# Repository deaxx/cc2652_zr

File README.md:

# cc2652_zr
ZB router on module E72-2G4M20S1E

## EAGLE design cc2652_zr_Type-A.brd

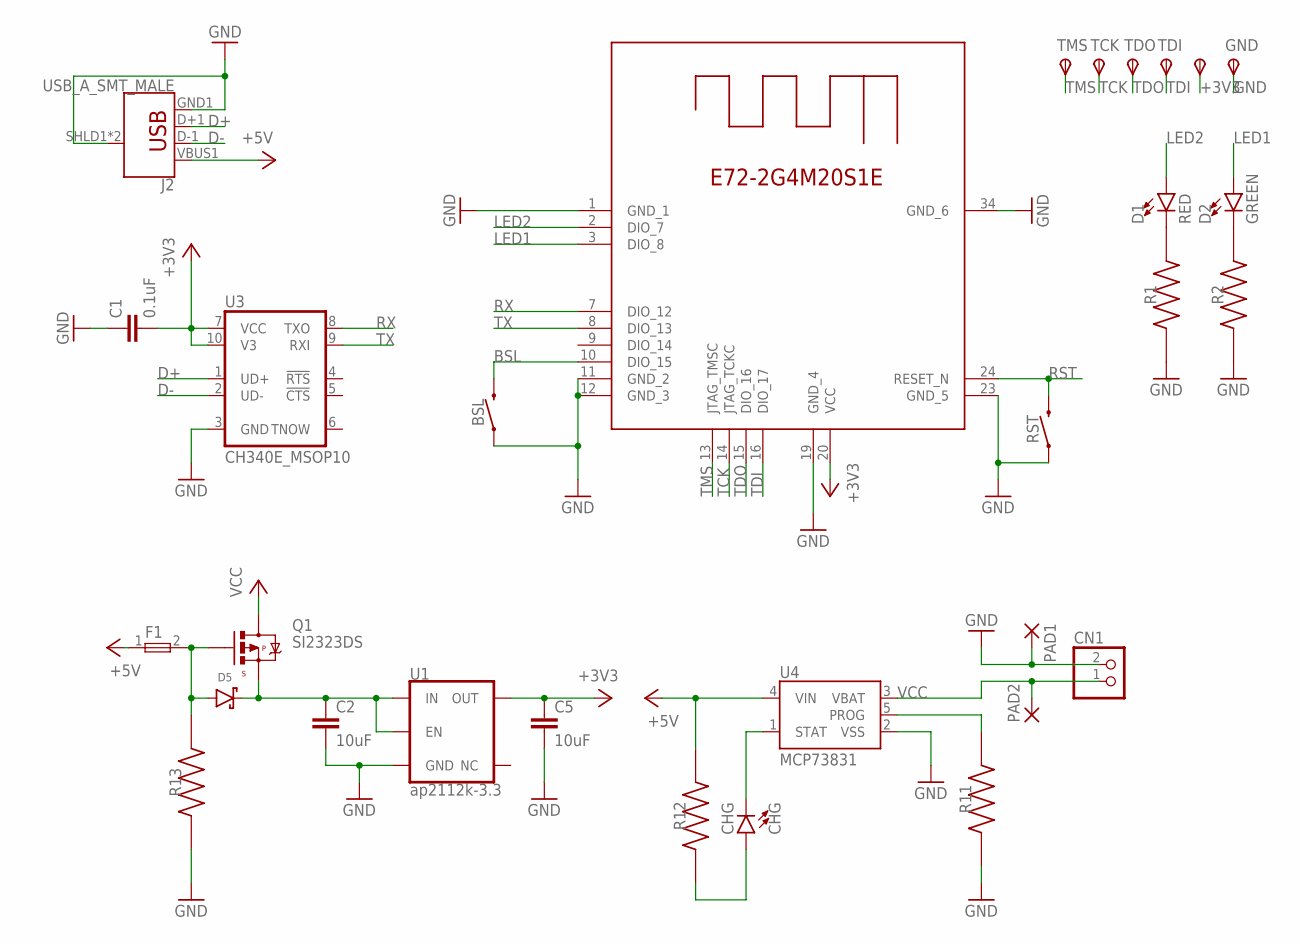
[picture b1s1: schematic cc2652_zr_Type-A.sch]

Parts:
+3V3: TPSTP11R; TP11R
BSL: MOMENTARY-SWITCH-SPST-SMD-4.6X2.8MM; TACTILE_SWITCH_SMD_4.6X2.8MM
C1: 0.1uF; 0603
C2, C5: 10uF; 0603
CHG: CHG; LED-0603
CN1: JST_2PIN-SMT-RA; JST-PH-2-SMT-RA
D1: RED; LED-0603
D2: GREEN; LED-0603
D5: DIODE-SCHOTTKY; SOD-323
F1: FEMTOSMDC016F-02; RESC1608X50N
GND: TPSTP11R; TP11R
J2: USB_A_SMT_MALE; USB-A-SMT-MALE
PAD1, PAD2: WIREPADSMD1,27-254; SMD1,27-2,54
Q1: SI2323DS; SOT23
R1, R2, R12: 2.2k; RESC1005X40N
R11: 2k; RESC1005X40N
R13: 10k; RESC1005X40N
RST: MOMENTARY-SWITCH-SPST-SMD-4.6X2.8MM; TACTILE_SWITCH_SMD_4.6X2.8MM
TCK: TPSTP11R; TP11R
TDI: TPSTP11R; TP11R
TDO: TPSTP11R; TP11R
TMS: TPSTP11R; TP11R
U1: ap2112k-3.3; SOT23-5
U3: CH340E_MSOP10; MSOP10
U4: MCP73831; SOT23-5
U$1: E72-2G4M20S1E

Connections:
+3V3: +3V3.TP, C1.2, C5.1, U1.5 (OUT), U3.7 (VCC), U3.10 (V3), U$1.20 (VCC)
+5V: F1.1, J2.VBUS1 (VBUS), R12.2, U4.4 (VIN)
BSL: BSL.3 (2), BSL.4 (2), U$1.10 (DIO_15)
D+: J2.D+1 (D+), U3.1 (UD+)
D-: J2.D-1 (D-), U3.2 (UD-)
GND: BSL.1, BSL.2 (1), C1.1, C2.2, C5.2, CN1.2 (1), GND.TP, J2.GND1 (GND), J2.SHLD1 (SHIELD), J2.SHLD2 (SHIELD), PAD1.1, R1.1, R2.1, R11.1, R13.1, RST.1, RST.2 (1), U1.2 (GND), U3.3 (GND), U4.2 (VSS), U$1.1 (GND_1), U$1.11 (GND_2), U$1.12 (GND_3), U$1.19 (GND_4), U$1.23 (GND_5), U$1.34 (GND_6)
LED1: D2.A, U$1.3 (DIO_8)
LED2: D1.A, U$1.2 (DIO_7)
unnamed: C2.1, D5.C, Q1.2 (S), U1.1 (IN), U1.3 (EN)
unnamed: D5.A, F1.2, Q1.1 (G), R13.2
unnamed: D1.C, R1.2
unnamed: D2.C, R2.2
unnamed: R11.2, U4.5 (PROG)
unnamed: CHG.A, R12.1
unnamed: CHG.C, U4.1 (STAT)
RST: RST.3 (2), RST.4 (2), U$1.24 (RESET_N)
RX: U3.8 (TXO), U$1.7 (DIO_12)
TCK: TCK.TP, U$1.14 (JTAG_TCKC)
TDI: TDI.TP, U$1.16 (DIO_17)
TDO: TDO.TP, U$1.15 (DIO_16)
TMS: TMS.TP, U$1.13 (JTAG_TMSC)
TX: U3.9 (RXI), U$1.8 (DIO_13)
VCC: CN1.1 (2), PAD2.1, Q1.3 (D), U4.3 (VBAT)

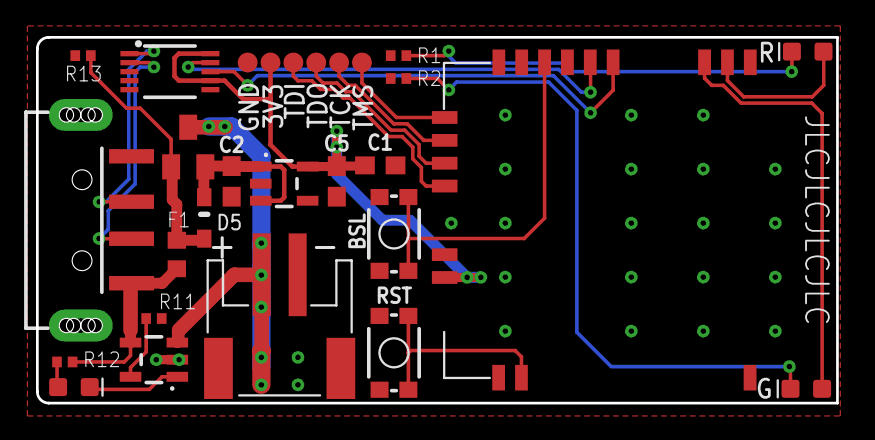
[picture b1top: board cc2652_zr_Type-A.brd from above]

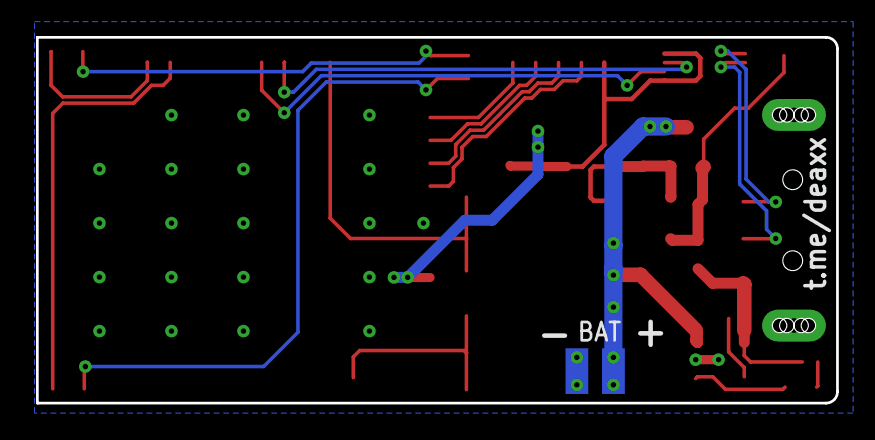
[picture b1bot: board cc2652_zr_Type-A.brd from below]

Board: 2 copper layers, 44.5 x 20.3 mm, 30 parts (2 on the bottom side), 23 nets.

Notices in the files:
parts and their libraries:
SparkFun-IC-Power: Licensing: Creative Commons ShareAlike 4.0 International - https://creativecommons.org/licenses/by-sa/4.0
